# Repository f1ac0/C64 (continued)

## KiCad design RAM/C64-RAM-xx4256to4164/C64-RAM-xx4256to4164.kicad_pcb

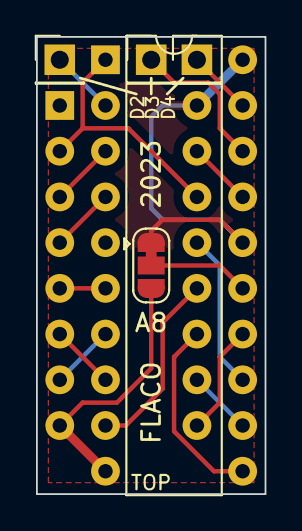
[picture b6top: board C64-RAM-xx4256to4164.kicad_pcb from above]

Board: 2 copper layers, 12.7 x 25.4 mm, 6 parts (0 on the bottom side), 18 nets.

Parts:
J2, J3, J4: D2; PinHeader_1x01_P2.54mm_Vertical
JP1: A8; SolderJumper-3_P1.3mm_Bridged12_RoundedPad1.0x1.5mm
U1: D4164; DIP-16_W7.62mm
U2: Dxx4256; DIP-20_W7.62mm

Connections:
+5V: JP1.3 (B), U1.8 (VCC), U2.10 (VCC)
/A0: U1.5 (A0), U2.6 (A0)
/A1: U1.7 (A1), U2.7 (A1)
/A2: U1.6 (A2), U2.8 (A2)
/A3: U1.12 (A3), U2.9 (A3)
/A4: U1.11 (A4), U2.11 (A4)
/A5: U1.10 (A5), U2.12 (A5)
/A6: U1.13 (A6), U2.13 (A6)
/A7: U1.9 (A7), U2.14 (A7)
/CAS: U1.15 (~CAS), U2.17 (~CAS)
/D1: U1.2 (DIN), U1.14 (DOUT), U2.1 (IO1)
/D2: J2.1, U2.2 (IO2)
/D3: J3.1, U2.18 (IO3)
/D4: J4.1, U2.19 (IO4)
/RAS: U1.4 (~RAS), U2.4 (~RAS)
/WE: U1.3 (~WE), U2.3 (~WE)
GND: JP1.1 (A), U1.16 (GND), U2.16 (~OE), U2.20 (GND)
unnamed: JP1.2 (C), U2.15 (A8)

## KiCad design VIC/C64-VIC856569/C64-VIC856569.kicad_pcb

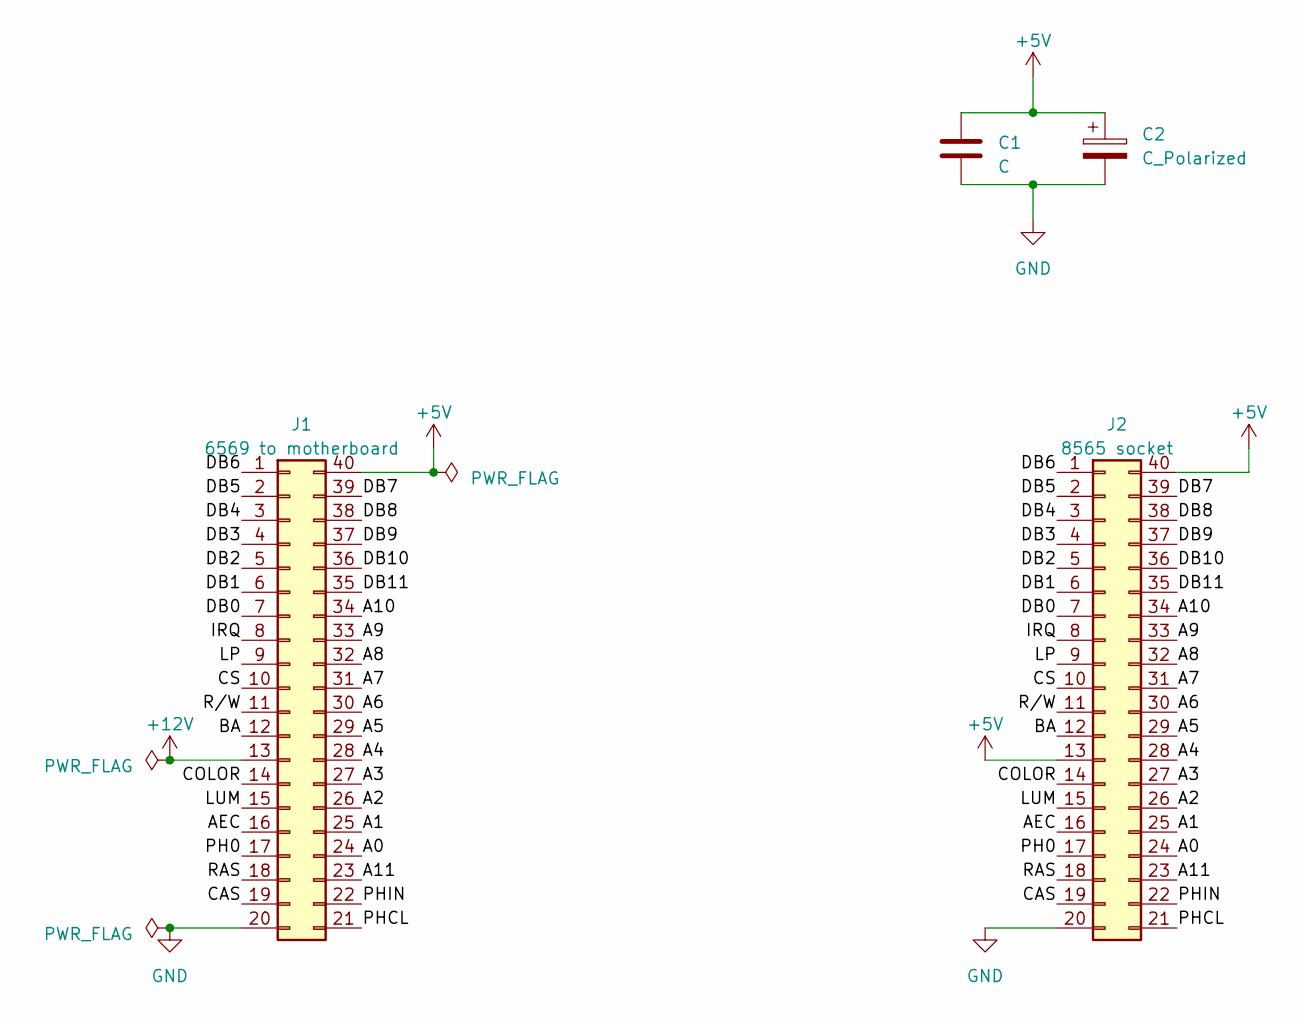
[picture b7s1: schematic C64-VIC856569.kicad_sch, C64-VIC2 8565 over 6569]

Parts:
C1: C; C_0805_2012Metric
C2: C_Polarized; CP_Radial_D5.0mm_P2.50mm
J1: 6569 to motherboard; DIP-40_W15.24mm
J2: 8565 socket; DIP-40_W15.24mm

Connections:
+5V: C1.1, C2.1, J1.40, J2.13, J2.40
+12V: J1.13
/A0: J1.24, J2.24
/A1: J1.25, J2.25
/A2: J1.26, J2.26
/A3: J1.27, J2.27
/A4: J1.28, J2.28
/A5: J1.29, J2.29
/A6: J1.30, J2.30
/A7: J1.31, J2.31
/A8: J1.32, J2.32
/A9: J1.33, J2.33
/A10: J1.34, J2.34
/A11: J1.23, J2.23
/AEC: J1.16, J2.16
/BA: J1.12, J2.12
/CAS: J1.19, J2.19
/COLOR: J1.14, J2.14
/CS: J1.10, J2.10
/DB0: J1.7, J2.7
/DB1: J1.6, J2.6
/DB2: J1.5, J2.5
/DB3: J1.4, J2.4
/DB4: J1.3, J2.3
/DB5: J1.2, J2.2
/DB6: J1.1, J2.1
/DB7: J1.39, J2.39
/DB8: J1.38, J2.38
/DB9: J1.37, J2.37
/DB10: J1.36, J2.36
/DB11: J1.35, J2.35
/IRQ: J1.8, J2.8
/LP: J1.9, J2.9
/LUM: J1.15, J2.15
/PH0: J1.17, J2.17
/PHCL: J1.21, J2.21
/PHIN: J1.22, J2.22
/RAS: J1.18, J2.18
/R/W: J1.11, J2.11
GND: C1.2, C2.2, J1.20, J2.20

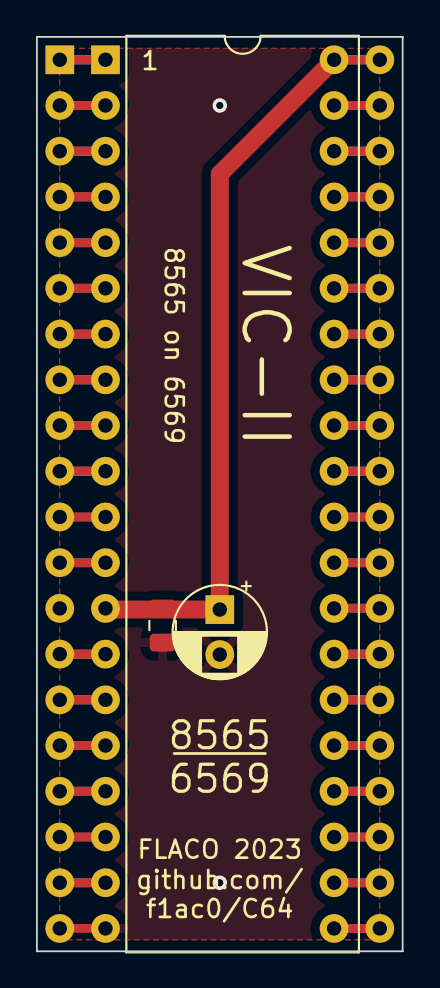
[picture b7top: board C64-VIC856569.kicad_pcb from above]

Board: 2 copper layers, 20.3 x 50.8 mm, 4 parts (0 on the bottom side), 39 nets.

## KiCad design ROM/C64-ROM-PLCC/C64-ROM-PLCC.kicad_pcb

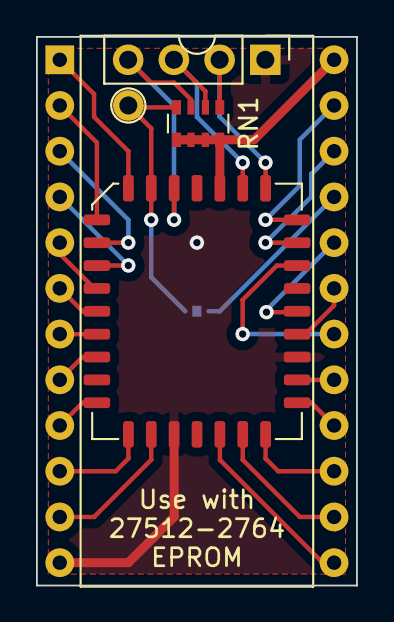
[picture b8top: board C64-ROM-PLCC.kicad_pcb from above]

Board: 2 copper layers, 17.8 x 30.5 mm, 6 parts (1 on the bottom side), 28 nets.

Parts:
J1: C64_ROM_socket; DIP-24_W15.24mm
J2: A13-15; PinHeader_1x04_P2.54mm_Vertical
J3: A12; TestPoint_THTPad_D1.7mm_Drill1.0mm
JP1: Jumper_2_Bridged; SolderJumper-2_P1.3mm_Bridged_RoundedPad1.0x1.5mm
RN1: 10k; R_Array_Convex_4x0603
U1: 27C512PLCC; PLCC-32_11.4x14.0mm_P1.27mm

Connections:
+5V: J1.24 (VCC), RN1.5 (R4.2), RN1.6 (R3.2), RN1.7 (R2.2), RN1.8 (R1.2), U1.32 (VCC)
/A0: J1.8 (A0), U1.11 (A0)
/A1: J1.7 (A1), U1.10 (A1)
/A2: J1.6 (A2), U1.9 (A2)
/A3: J1.5 (A3), U1.8 (A3)
/A4: J1.4 (A4), U1.7 (A4)
/A5: J1.3 (A5), U1.6 (A5)
/A6: J1.2 (A6), U1.5 (A6)
/A7: J1.1 (A7), U1.4 (A7)
/A8: J1.23 (A8), U1.29 (A8)
/A9: J1.22 (A9), U1.28 (A9)
/A10: J1.19 (A10), U1.24 (A10)
/A11: J1.18 (A11), U1.27 (A11)
/A12: J1.21 (A12), JP1.1 (A)
/D0: J1.9 (D0), U1.13 (O0)
/D1: J1.10 (D1), U1.14 (O1)
/D2: J1.11 (D2), U1.15 (O2)
/D3: J1.13 (D3), U1.18 (O3)
/D4: J1.14 (D4), U1.19 (O4)
/D5: J1.15 (D5), U1.20 (O5)
/D6: J1.16 (D6), U1.21 (O6)
/D7: J1.17 (D7), U1.22 (O7)
/ROMA12: J3.1, JP1.2 (B), RN1.4 (R4.1), U1.3 (A12)
/ROMA13: J2.2, RN1.1 (R1.1), U1.30 (A13)
/ROMA14: J2.3, RN1.2 (R2.1), U1.31 (A14)
/ROMA15: J2.4, RN1.3 (R3.1), U1.2 (A15)
//CE: J1.20 (~CE), U1.25 (~OE/VPP)
GND: J1.12 (GND), J2.1, U1.16 (GND), U1.23 (~CE)

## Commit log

2023-03-06 Respository init with KiCAD files, Readme and License
2023-03-06 Readme typo
2023-05-30 Addition of Cartridge/C64-Cartridge to support DIP32 EEPROMs. Addition of Interactive Boms.
2023-06-02 Addition of C64-KungFuFlash : a reworked PCB with different footprints and reworked routing.
2023-06-02 Addition of C64-KungFuFlash Interactive Bom.
2023-07-01 Addition of Cartridge/C64-Cartridge missing files that should have been in a commit 2 monts ago...
2024-01-21 C64-Cartridge : addition of EpyxFastload daughter board ; some silkscreen changes. C64-KungFuFlash, C64-Pi1541 : small updates before production. New C64-efuse board that fit inside the DIN plug.
